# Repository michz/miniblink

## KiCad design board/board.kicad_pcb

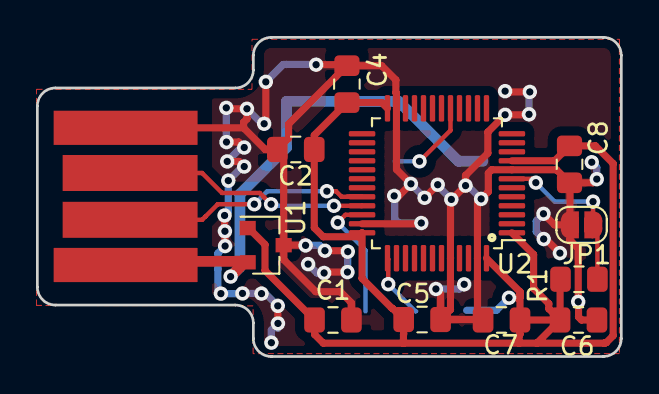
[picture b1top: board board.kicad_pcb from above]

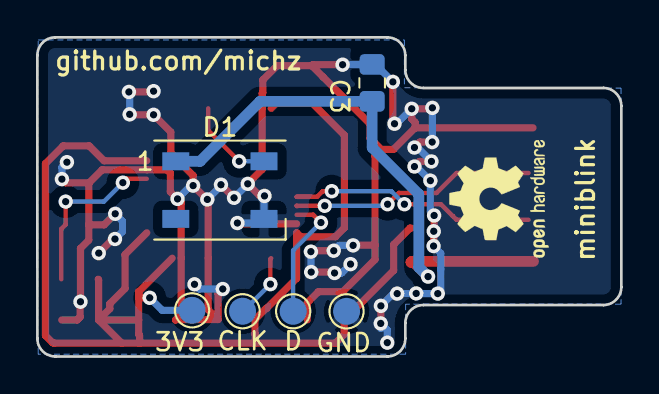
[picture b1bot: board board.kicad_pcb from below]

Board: 2 copper layers, 32.4 x 17.7 mm, 18 parts (6 on the bottom side), 9 nets.

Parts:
3V3: SWVCC; TestPoint_Pad_D1.5mm
C1: 1u; C_0805_2012Metric_Pad1.15x1.40mm_HandSolder
C2: 2u2; C_0805_2012Metric_Pad1.15x1.40mm_HandSolder
C3, C4, C5, C6, C7, C8: 100n; C_0805_2012Metric_Pad1.15x1.40mm_HandSolder
CLK: SWCLK; TestPoint_Pad_D1.5mm
D: SWDIO; TestPoint_Pad_D1.5mm
D1: WS2812B; LED_WS2812B_PLCC4_5.0x5.0mm_P3.2mm
GND: SWGND; TestPoint_Pad_D1.5mm
J5: USB_A; usb-PCB
JP1: RST; SolderJumper-2_P1.3mm_Open_RoundedPad1.0x1.5mm
R1: 10k; R_0805_2012Metric_Pad1.15x1.40mm_HandSolder
U1: TS5204; SOT-23
U2: STM32L073CBTx; LQFP-48_7x7mm_P0.5mm

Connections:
+3V3: 3V3.1, C1.1, C2.1, C4.1, C5.1, C6.1, C7.1, C8.1, R1.1, U1.1, U2.1, U2.9, U2.24, U2.36, U2.48
+5V: C3.1, D1.1, J5.1, U1.2
/LED: D1.4, U2.17
/USB_M: J5.2, U2.32
/USB_P: J5.3, U2.33
GND: C1.2, C2.2, C3.2, C4.2, C5.2, C6.2, C7.2, C8.2, D1.3, GND.1, J5.4, JP1.2, U1.3, U2.8, U2.23, U2.35, U2.44, U2.47
unnamed: D.1, U2.34
unnamed: CLK.1, U2.37
unnamed: JP1.1, R1.2, U2.7

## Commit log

2019-07-28 add very first version
2019-10-12 minimal working example with USB CDC
    (without LED!)
